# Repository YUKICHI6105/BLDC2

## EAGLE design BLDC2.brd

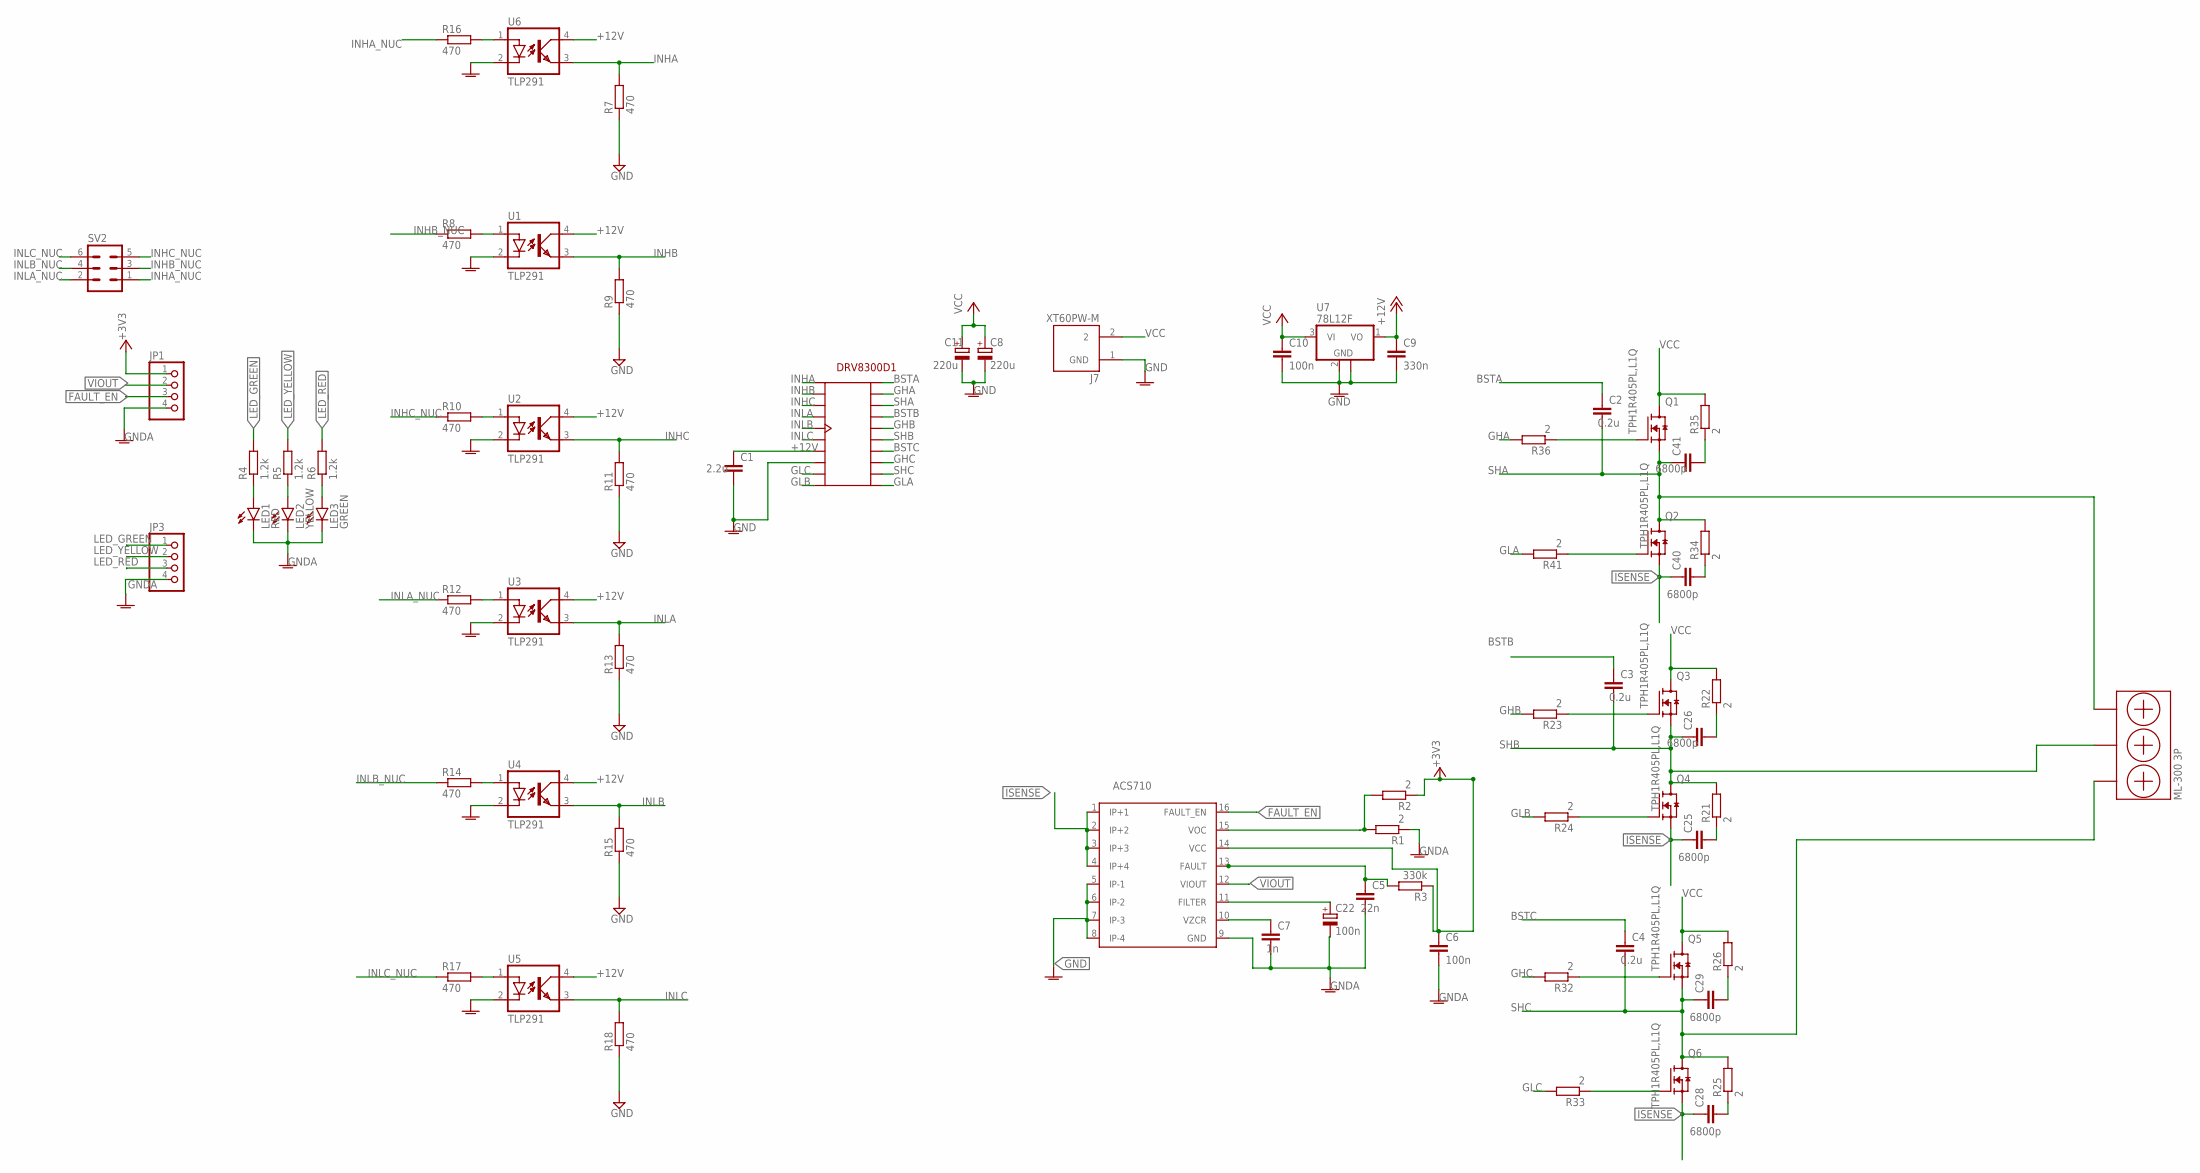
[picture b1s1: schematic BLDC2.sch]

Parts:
C1: 2.2u; C1206
C2, C3, C4: 0.2u; C1206
C5: 22n; C0603
C6, C10: 100n; C0603
C7: 1n; C0603
C8, C11: 220u; E5-10,5
C9: 330n; C0603
C22: 100n; E2,5-5
C25, C26, C28, C29, C40, C41: 6800p; C0603
DRV8300D1: DRV8300D
J7: XT60PW-M; AMASS_XT60PW-M
JP1, JP3: PINHD-1X4; 1X04
LED1: RED; CHIP-LED0603
LED2: YELLOW; CHIP-LED0603
LED3: GREEN; CHIP-LED0603
ML-300-3P1: ML-300-3P; ML300-3P
Q1, Q2, Q3, Q4, Q5, Q6: TPH1R405PL,L1Q; SOPADVANCE
R1, R2, R21, R22, R23, R24, R25, R26, R32, R33, R34, R35, R36, R41: 2; R0603
R3: 330k; R0603
R4, R5, R6: 1.2k; R0603
R7, R8, R9, R10, R11, R12, R13, R14, R15, R16, R17, R18: 470; R0603
SV2: MA03-2
U1, U2, U3, U4, U5, U6: TLP291; MINI-FLAT-4
U7: 78L12F; SOT89
U$1: ACS710

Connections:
+3V3: C6.1, JP1.1, R2.1, R3.1, U$1.14 (VCC)
+12V: C1.1, C9.1, DRV8300D1.GVDD, U1.4 (COL), U2.4 (COL), U3.4 (COL), U4.4 (COL), U5.4 (COL), U6.4 (COL), U7.1 (VO)
AHG1: Q1.4 (G), R36.1
AHG3: Q3.4 (G), R23.1
AHG4: Q5.4 (G), R32.1
ALG1: Q2.4 (G), R41.1
ALG3: Q4.4 (G), R24.1
ALG4: Q6.4 (G), R33.1
BSTA: C2.1, DRV8300D1.BSTA
BSTB: C3.1, DRV8300D1.BSTB
BSTC: C4.1, DRV8300D1.BSTC
FAULT_EN: JP1.3, U$1.16 (FAULT_EN)
GHA: DRV8300D1.GHA, R36.2
GHB: DRV8300D1.GHB, R23.2
GHC: DRV8300D1.GHC, R32.2
GLA: DRV8300D1.GLA, R41.2
GLB: DRV8300D1.GLB, R24.2
GLC: DRV8300D1.GLC, R33.2
GND: C1.2, C8.-, C9.2, C10.2, C11.-, DRV8300D1.GND, J7.1 (GND), R7.1, R9.1, R11.1, R13.1, R15.1, R18.1, U7.2 (GND), U7.2@1 (GND), U$1.5 (IP-1), U$1.6 (IP-2), U$1.7 (IP-3), U$1.8 (IP-4)
GNDA: C5.2, C6.2, C7.2, C22.-, JP1.4, JP3.4, LED1.C, LED2.C, LED3.C, R1.1, U1.2 (C), U2.2 (C), U3.2 (C), U4.2 (C), U5.2 (C), U6.2 (C), U$1.9 (GND)
INHA: DRV8300D1.INHA, R7.2, U6.3 (EMIT)
INHA_NUC: R16.1, SV2.1
INHB: DRV8300D1.INHB, R9.2, U1.3 (EMIT)
INHB_NUC: R8.1, SV2.3
INHC: DRV8300D1.INHC, R11.2, U2.3 (EMIT)
INHC_NUC: R10.1, SV2.5
INLA: DRV8300D1.INLA, R13.2, U3.3 (EMIT)
INLA_NUC: R12.1, SV2.2
INLB: DRV8300D1.INLB, R15.2, U4.3 (EMIT)
INLB_NUC: R14.1, SV2.4
INLC: DRV8300D1.INLC, R18.2, U5.3 (EMIT)
INLC_NUC: R17.1, SV2.6
ISENSE: C25.1, C28.1, C40.1, Q2.1 (S), Q2.2 (S), Q2.3 (S), Q4.1 (S), Q4.2 (S), Q4.3 (S), Q6.1 (S), Q6.2 (S), Q6.3 (S), U$1.1 (IP+1), U$1.2 (IP+2), U$1.3 (IP+3), U$1.4 (IP+4)
LED_GREEN: JP3.1, R4.2
LED_RED: JP3.3, R6.2
LED_YELLOW: JP3.2, R5.2
unnamed: LED1.A, R4.1
unnamed: LED2.A, R5.1
unnamed: R1.2, R2.2, U$1.15 (VOC)
unnamed: C5.1, R3.2, U$1.13 (FAULT)
unnamed: C7.1, U$1.10 (VZCR)
unnamed: LED3.A, R6.1
unnamed: R8.2, U1.1 (A)
unnamed: R10.2, U2.1 (A)
unnamed: R12.2, U3.1 (A)
unnamed: R14.2, U4.1 (A)
unnamed: R17.2, U5.1 (A)
unnamed: C22.+, U$1.11 (FILTER)
unnamed: R16.2, U6.1 (A)
unnamed: C25.2, R21.1
unnamed: C26.2, R22.1
unnamed: C28.2, R25.1
unnamed: C29.2, R26.1
unnamed: C40.2, R34.1
unnamed: C41.2, R35.1
SHA: C2.2, C41.1, DRV8300D1.SHA, ML-300-3P1.P$1, Q1.1 (S), Q1.2 (S), Q1.3 (S), Q2.5 (D), Q2.6 (D), Q2.7 (D), Q2.8 (D), Q2.9 (D), R34.2
SHB: C3.2, C26.1, DRV8300D1.SHB, ML-300-3P1.P$3, Q3.1 (S), Q3.2 (S), Q3.3 (S), Q4.5 (D), Q4.6 (D), Q4.7 (D), Q4.8 (D), Q4.9 (D), R21.2
SHC: C4.2, C29.1, DRV8300D1.SHC, ML-300-3P1.P$5, Q5.1 (S), Q5.2 (S), Q5.3 (S), Q6.5 (D), Q6.6 (D), Q6.7 (D), Q6.8 (D), Q6.9 (D), R25.2
VCC: C8.+, C10.1, C11.+, J7.2, Q1.5 (D), Q1.6 (D), Q1.7 (D), Q1.8 (D), Q1.9 (D), Q3.5 (D), Q3.6 (D), Q3.7 (D), Q3.8 (D), Q3.9 (D), Q5.5 (D), Q5.6 (D), Q5.7 (D), Q5.8 (D), Q5.9 (D), R22.2, R26.2, R35.2, U7.3 (VI)
VIOUT: JP1.2, U$1.12 (VIOUT)

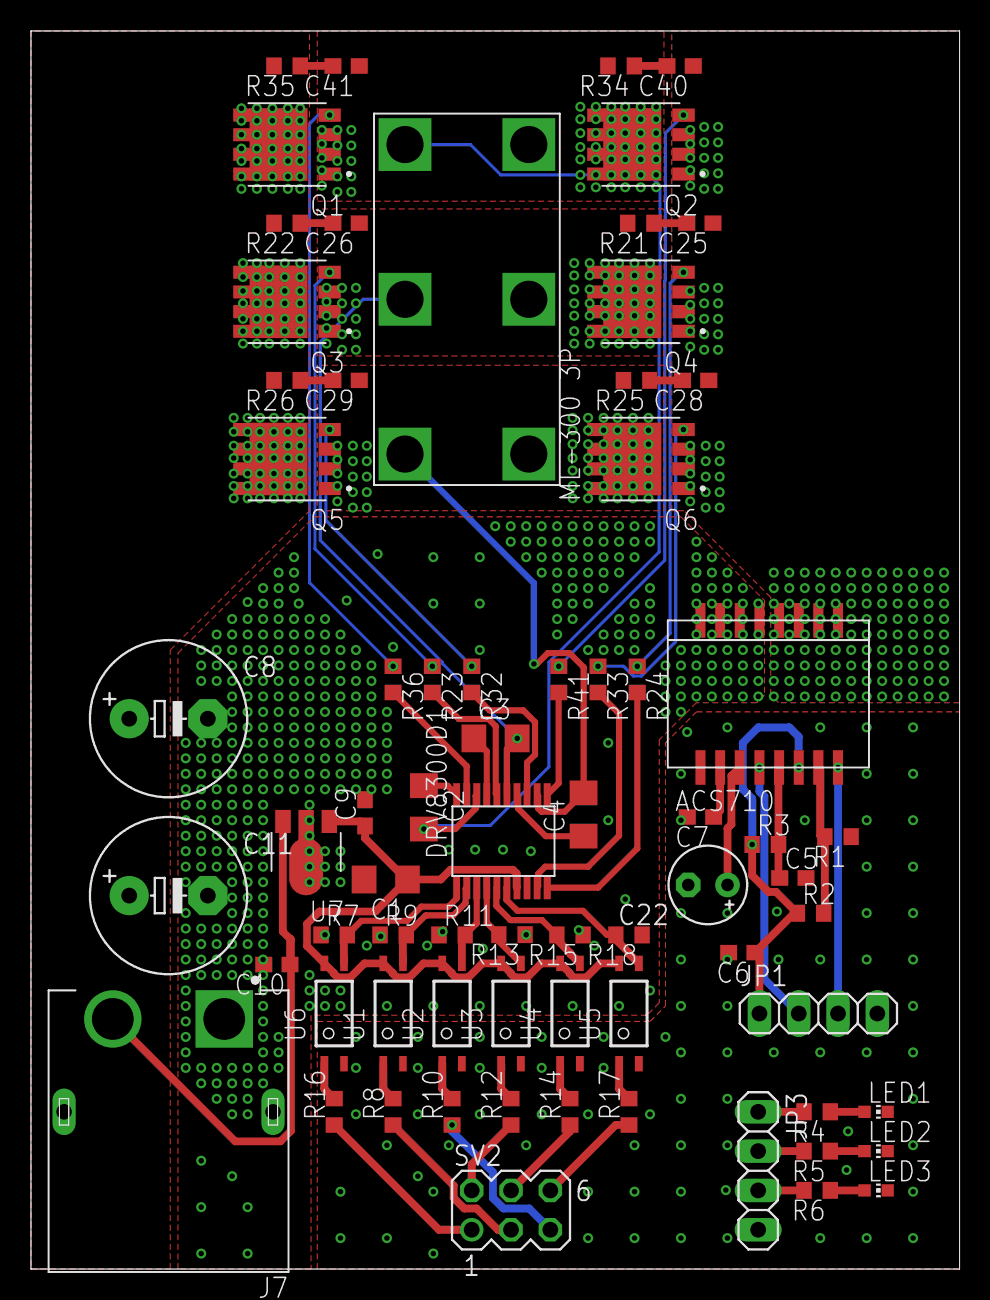
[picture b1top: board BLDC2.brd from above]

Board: 2 copper layers, 60.0 x 80.0 mm, 71 parts (0 on the bottom side), 60 nets.

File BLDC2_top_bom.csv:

Comment,Designator,Footprint,LCSC Part #
0.2u,C2 C3 C4,C1206,
1.2k,R4 R5 R6,R0603,
1n,C7,C0603,
2,R1 R2 R21 R22 R23 R24 R25 R26 R32 R33 R34 R35 R36 R41,R0603,
2.2u,C1,C1206,
22n,C5,C0603,
78L12F,U7,SOT89,
100n,C6 C10,C0603,
330k,R3,R0603,
330n,C9,C0603,
470,R7 R8 R9 R10 R11 R12 R13 R14 R15 R16 R17 R18,R0603,
6800p,C25 C26 C28 C29 C40 C41,C0603,
ACS710,U$1,ACS710,
DRV8300D,DRV8300D1,DRV8300D,
GREEN,LED3,CHIP-LED0603,
RED,LED1,CHIP-LED0603,
TLP291,U1 U2 U3 U4 U5 U6,MINI-FLAT-4,
TPH1R405PL L1Q,Q1,SOPADVANCE,
TPH1R405PL L1Q,Q2,SOPADVANCE,
TPH1R405PL L1Q,Q3,SOPADVANCE,
TPH1R405PL L1Q,Q4,SOPADVANCE,
TPH1R405PL L1Q,Q5,SOPADVANCE,
TPH1R405PL L1Q,Q6,SOPADVANCE,
YELLOW,LED2,CHIP-LED0603,
